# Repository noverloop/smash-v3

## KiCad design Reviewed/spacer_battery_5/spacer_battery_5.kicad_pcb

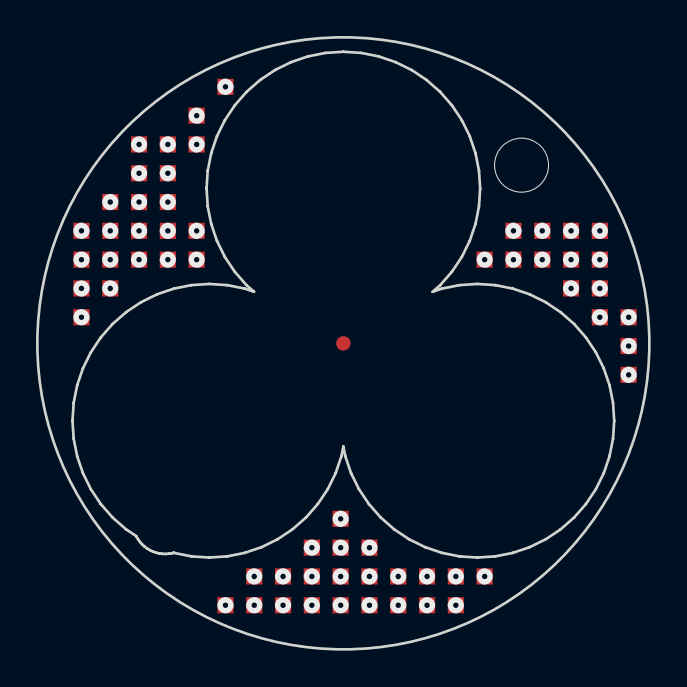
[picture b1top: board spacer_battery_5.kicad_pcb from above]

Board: 2 copper layers, 34.0 x 34.0 mm, 3 parts (1 on the bottom side), 46 nets, no tracks yet.

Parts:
J_spacer_battery_5_top: LGA_lands; J_spacer_battery_5_top
P_spacer_battery_5_bot: LGA_lands; P_spacer_battery_5_bot
SP_battery_5: SP_battery_5; Spacer_Mechanical_34mm

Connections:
3V3: J_spacer_battery_5_top.23, J_spacer_battery_5_top.47, J_spacer_battery_5_top.52, P_spacer_battery_5_bot.23, P_spacer_battery_5_bot.47, P_spacer_battery_5_bot.52
3V3_AON: J_spacer_battery_5_top.24, J_spacer_battery_5_top.48, P_spacer_battery_5_bot.24, P_spacer_battery_5_bot.48
ACTIVATE_CONFIRM: J_spacer_battery_5_top.3, P_spacer_battery_5_bot.3
ACTIVATE_SET: J_spacer_battery_5_top.4, P_spacer_battery_5_bot.4
BAT_PROT: J_spacer_battery_5_top.5, J_spacer_battery_5_top.49, P_spacer_battery_5_bot.5, P_spacer_battery_5_bot.49
BAT_RAW: J_spacer_battery_5_top.6, J_spacer_battery_5_top.50, P_spacer_battery_5_bot.6, P_spacer_battery_5_bot.50
BOOT0: J_spacer_battery_5_top.7, P_spacer_battery_5_bot.7
COMP_5V: J_spacer_battery_5_top.8, J_spacer_battery_5_top.51, P_spacer_battery_5_bot.8, P_spacer_battery_5_bot.51
COMP_SWDCLK: J_spacer_battery_5_top.9, P_spacer_battery_5_bot.9
COMP_SWDIO: J_spacer_battery_5_top.10, P_spacer_battery_5_bot.10
EXT_CAN_RX: J_spacer_battery_5_top.11, P_spacer_battery_5_bot.11
EXT_CAN_TX: J_spacer_battery_5_top.14, P_spacer_battery_5_bot.14
FIN1_AOUT1: J_spacer_battery_5_top.13, P_spacer_battery_5_bot.13
FIN1_AOUT2: J_spacer_battery_5_top.12, P_spacer_battery_5_bot.12
FIN1_BOUT1: J_spacer_battery_5_top.15, P_spacer_battery_5_bot.15
FIN1_BOUT2: J_spacer_battery_5_top.16, P_spacer_battery_5_bot.16
FIN2_AOUT1: J_spacer_battery_5_top.17, P_spacer_battery_5_bot.17
FIN2_AOUT2: J_spacer_battery_5_top.18, P_spacer_battery_5_bot.18
FIN2_BOUT1: J_spacer_battery_5_top.19, P_spacer_battery_5_bot.19
FIN2_BOUT2: J_spacer_battery_5_top.20, P_spacer_battery_5_bot.20
FIN3_AOUT1: J_spacer_battery_5_top.21, P_spacer_battery_5_bot.21
FIN3_AOUT2: J_spacer_battery_5_top.22, P_spacer_battery_5_bot.22
FIN3_BOUT1: J_spacer_battery_5_top.1, P_spacer_battery_5_bot.1
FIN3_BOUT2: J_spacer_battery_5_top.2, P_spacer_battery_5_bot.2
FIN4_AOUT1: J_spacer_battery_5_top.25, P_spacer_battery_5_bot.25
FIN4_AOUT2: J_spacer_battery_5_top.26, P_spacer_battery_5_bot.26
FIN4_BOUT1: J_spacer_battery_5_top.27, P_spacer_battery_5_bot.27
FIN4_BOUT2: J_spacer_battery_5_top.28, P_spacer_battery_5_bot.28
FIN_HALL: J_spacer_battery_5_top.29, P_spacer_battery_5_bot.29
FLEX_GND: J_spacer_battery_5_top.30, J_spacer_battery_5_top.53, J_spacer_battery_5_top.54, J_spacer_battery_5_top.55, J_spacer_battery_5_top.56, J_spacer_battery_5_top.57, J_spacer_battery_5_top.58, J_spacer_battery_5_top.59, J_spacer_battery_5_top.60, P_spacer_battery_5_bot.30, P_spacer_battery_5_bot.53, P_spacer_battery_5_bot.54, P_spacer_battery_5_bot.55, P_spacer_battery_5_bot.56, P_spacer_battery_5_bot.57, P_spacer_battery_5_bot.58, P_spacer_battery_5_bot.59, P_spacer_battery_5_bot.60, SP_battery_5.1
GPIO_EXT_0: J_spacer_battery_5_top.31, P_spacer_battery_5_bot.31
GPIO_EXT_1: J_spacer_battery_5_top.32, P_spacer_battery_5_bot.32
GPIO_EXT_2: J_spacer_battery_5_top.33, P_spacer_battery_5_bot.33
GPIO_EXT_3: J_spacer_battery_5_top.34, P_spacer_battery_5_bot.34
H3LIS_INT1: J_spacer_battery_5_top.35, P_spacer_battery_5_bot.35
I2C3_SCL: J_spacer_battery_5_top.36, P_spacer_battery_5_bot.36
I2C3_SDA: J_spacer_battery_5_top.37, P_spacer_battery_5_bot.37
JUMP_WAKE: J_spacer_battery_5_top.38, P_spacer_battery_5_bot.38
NRST: J_spacer_battery_5_top.39, P_spacer_battery_5_bot.39
SWO: J_spacer_battery_5_top.40, P_spacer_battery_5_bot.40
SYS_I2C_SCL: J_spacer_battery_5_top.41, P_spacer_battery_5_bot.41
SYS_I2C_SDA: J_spacer_battery_5_top.42, P_spacer_battery_5_bot.42
SYS_SPI_CS_FIN: J_spacer_battery_5_top.43, P_spacer_battery_5_bot.43
SYS_SPI_MISO: J_spacer_battery_5_top.44, P_spacer_battery_5_bot.44
SYS_SPI_MOSI: J_spacer_battery_5_top.45, P_spacer_battery_5_bot.45
SYS_SPI_SCLK: J_spacer_battery_5_top.46, P_spacer_battery_5_bot.46

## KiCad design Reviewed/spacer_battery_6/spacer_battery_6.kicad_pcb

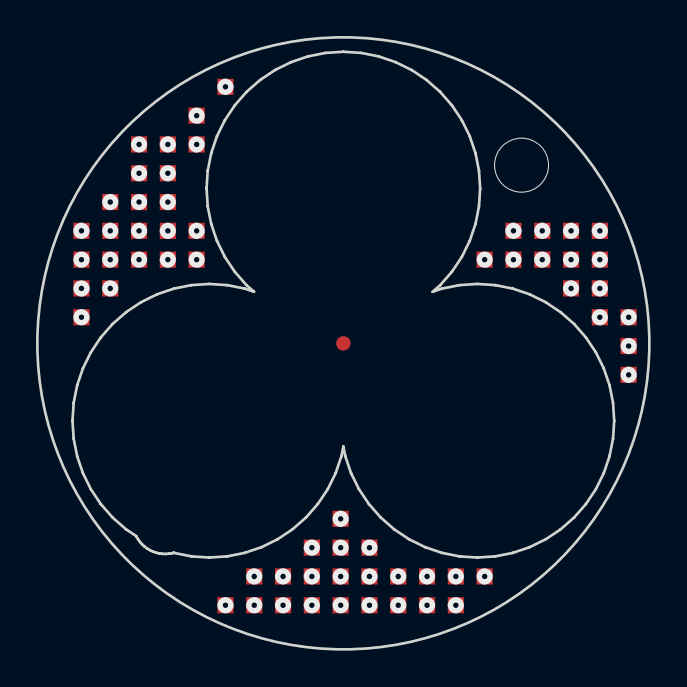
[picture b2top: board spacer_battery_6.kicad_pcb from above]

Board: 2 copper layers, 34.0 x 34.0 mm, 3 parts (1 on the bottom side), 46 nets, no tracks yet.

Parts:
J_spacer_battery_6_top: LGA_lands; J_spacer_battery_6_top
P_spacer_battery_6_bot: LGA_lands; P_spacer_battery_6_bot
SP_battery_6: SP_battery_6; Spacer_Mechanical_34mm

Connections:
3V3: J_spacer_battery_6_top.23, J_spacer_battery_6_top.47, J_spacer_battery_6_top.52, P_spacer_battery_6_bot.23, P_spacer_battery_6_bot.47, P_spacer_battery_6_bot.52
3V3_AON: J_spacer_battery_6_top.24, J_spacer_battery_6_top.48, P_spacer_battery_6_bot.24, P_spacer_battery_6_bot.48
ACTIVATE_CONFIRM: J_spacer_battery_6_top.3, P_spacer_battery_6_bot.3
ACTIVATE_SET: J_spacer_battery_6_top.4, P_spacer_battery_6_bot.4
BAT_PROT: J_spacer_battery_6_top.5, J_spacer_battery_6_top.49, P_spacer_battery_6_bot.5, P_spacer_battery_6_bot.49
BAT_RAW: J_spacer_battery_6_top.6, J_spacer_battery_6_top.50, P_spacer_battery_6_bot.6, P_spacer_battery_6_bot.50
BOOT0: J_spacer_battery_6_top.7, P_spacer_battery_6_bot.7
COMP_5V: J_spacer_battery_6_top.8, J_spacer_battery_6_top.51, P_spacer_battery_6_bot.8, P_spacer_battery_6_bot.51
COMP_SWDCLK: J_spacer_battery_6_top.9, P_spacer_battery_6_bot.9
COMP_SWDIO: J_spacer_battery_6_top.10, P_spacer_battery_6_bot.10
EXT_CAN_RX: J_spacer_battery_6_top.11, P_spacer_battery_6_bot.11
EXT_CAN_TX: J_spacer_battery_6_top.14, P_spacer_battery_6_bot.14
FIN1_AOUT1: J_spacer_battery_6_top.13, P_spacer_battery_6_bot.13
FIN1_AOUT2: J_spacer_battery_6_top.12, P_spacer_battery_6_bot.12
FIN1_BOUT1: J_spacer_battery_6_top.15, P_spacer_battery_6_bot.15
FIN1_BOUT2: J_spacer_battery_6_top.16, P_spacer_battery_6_bot.16
FIN2_AOUT1: J_spacer_battery_6_top.17, P_spacer_battery_6_bot.17
FIN2_AOUT2: J_spacer_battery_6_top.18, P_spacer_battery_6_bot.18
FIN2_BOUT1: J_spacer_battery_6_top.19, P_spacer_battery_6_bot.19
FIN2_BOUT2: J_spacer_battery_6_top.20, P_spacer_battery_6_bot.20
FIN3_AOUT1: J_spacer_battery_6_top.21, P_spacer_battery_6_bot.21
FIN3_AOUT2: J_spacer_battery_6_top.22, P_spacer_battery_6_bot.22
FIN3_BOUT1: J_spacer_battery_6_top.1, P_spacer_battery_6_bot.1
FIN3_BOUT2: J_spacer_battery_6_top.2, P_spacer_battery_6_bot.2
FIN4_AOUT1: J_spacer_battery_6_top.25, P_spacer_battery_6_bot.25
FIN4_AOUT2: J_spacer_battery_6_top.26, P_spacer_battery_6_bot.26
FIN4_BOUT1: J_spacer_battery_6_top.27, P_spacer_battery_6_bot.27
FIN4_BOUT2: J_spacer_battery_6_top.28, P_spacer_battery_6_bot.28
FIN_HALL: J_spacer_battery_6_top.29, P_spacer_battery_6_bot.29
FLEX_GND: J_spacer_battery_6_top.30, J_spacer_battery_6_top.53, J_spacer_battery_6_top.54, J_spacer_battery_6_top.55, J_spacer_battery_6_top.56, J_spacer_battery_6_top.57, J_spacer_battery_6_top.58, J_spacer_battery_6_top.59, J_spacer_battery_6_top.60, P_spacer_battery_6_bot.30, P_spacer_battery_6_bot.53, P_spacer_battery_6_bot.54, P_spacer_battery_6_bot.55, P_spacer_battery_6_bot.56, P_spacer_battery_6_bot.57, P_spacer_battery_6_bot.58, P_spacer_battery_6_bot.59, P_spacer_battery_6_bot.60, SP_battery_6.1
GPIO_EXT_0: J_spacer_battery_6_top.31, P_spacer_battery_6_bot.31
GPIO_EXT_1: J_spacer_battery_6_top.32, P_spacer_battery_6_bot.32
GPIO_EXT_2: J_spacer_battery_6_top.33, P_spacer_battery_6_bot.33
GPIO_EXT_3: J_spacer_battery_6_top.34, P_spacer_battery_6_bot.34
H3LIS_INT1: J_spacer_battery_6_top.35, P_spacer_battery_6_bot.35
I2C3_SCL: J_spacer_battery_6_top.36, P_spacer_battery_6_bot.36
I2C3_SDA: J_spacer_battery_6_top.37, P_spacer_battery_6_bot.37
JUMP_WAKE: J_spacer_battery_6_top.38, P_spacer_battery_6_bot.38
NRST: J_spacer_battery_6_top.39, P_spacer_battery_6_bot.39
SWO: J_spacer_battery_6_top.40, P_spacer_battery_6_bot.40
SYS_I2C_SCL: J_spacer_battery_6_top.41, P_spacer_battery_6_bot.41
SYS_I2C_SDA: J_spacer_battery_6_top.42, P_spacer_battery_6_bot.42
SYS_SPI_CS_FIN: J_spacer_battery_6_top.43, P_spacer_battery_6_bot.43
SYS_SPI_MISO: J_spacer_battery_6_top.44, P_spacer_battery_6_bot.44
SYS_SPI_MOSI: J_spacer_battery_6_top.45, P_spacer_battery_6_bot.45
SYS_SPI_SCLK: J_spacer_battery_6_top.46, P_spacer_battery_6_bot.46

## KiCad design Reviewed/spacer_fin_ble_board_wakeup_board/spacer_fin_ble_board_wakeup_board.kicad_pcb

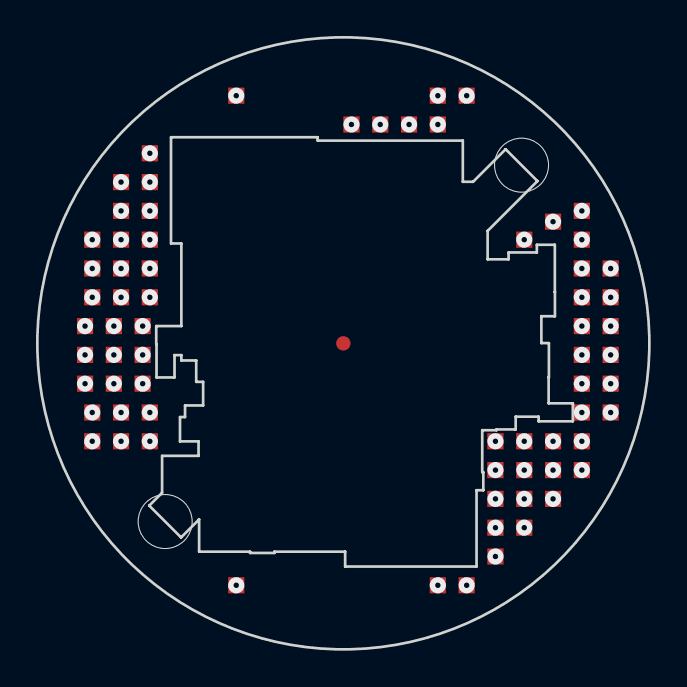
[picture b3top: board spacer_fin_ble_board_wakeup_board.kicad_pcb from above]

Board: 2 copper layers, 34.0 x 34.0 mm, 3 parts (1 on the bottom side), 34 nets, no tracks yet.

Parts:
J_spacer_fin_ble_board_wakeup_board_top: LGA_lands; J_spacer_fin_ble_board_wakeup_board_top
P_spacer_fin_ble_board_wakeup_board_bot: LGA_lands; P_spacer_fin_ble_board_wakeup_board_bot
SP_fin_ble_board_wakeup_board: SP_fin_ble_board_wakeup_board; Spacer_Mechanical_34mm

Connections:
3V3: J_spacer_fin_ble_board_wakeup_board_top.1, J_spacer_fin_ble_board_wakeup_board_top.35, J_spacer_fin_ble_board_wakeup_board_top.41, P_spacer_fin_ble_board_wakeup_board_bot.1, P_spacer_fin_ble_board_wakeup_board_bot.35, P_spacer_fin_ble_board_wakeup_board_bot.41
3V3_AON: J_spacer_fin_ble_board_wakeup_board_top.2, J_spacer_fin_ble_board_wakeup_board_top.36, P_spacer_fin_ble_board_wakeup_board_bot.2, P_spacer_fin_ble_board_wakeup_board_bot.36
ACTIVATE_CONFIRM: J_spacer_fin_ble_board_wakeup_board_top.3, P_spacer_fin_ble_board_wakeup_board_bot.3
ACTIVATE_SET: J_spacer_fin_ble_board_wakeup_board_top.4, P_spacer_fin_ble_board_wakeup_board_bot.4
BAT_CELL1_POS: J_spacer_fin_ble_board_wakeup_board_top.5, P_spacer_fin_ble_board_wakeup_board_bot.5
BAT_CELL2_POS: J_spacer_fin_ble_board_wakeup_board_top.6, P_spacer_fin_ble_board_wakeup_board_bot.6
BAT_CELL3_POS: J_spacer_fin_ble_board_wakeup_board_top.7, P_spacer_fin_ble_board_wakeup_board_bot.7
BAT_PROT: J_spacer_fin_ble_board_wakeup_board_top.8, J_spacer_fin_ble_board_wakeup_board_top.37, P_spacer_fin_ble_board_wakeup_board_bot.8, P_spacer_fin_ble_board_wakeup_board_bot.37
BAT_RAW: J_spacer_fin_ble_board_wakeup_board_top.9, J_spacer_fin_ble_board_wakeup_board_top.38, P_spacer_fin_ble_board_wakeup_board_bot.9, P_spacer_fin_ble_board_wakeup_board_bot.38
BOOT0: J_spacer_fin_ble_board_wakeup_board_top.10, P_spacer_fin_ble_board_wakeup_board_bot.10
COMP_5V: J_spacer_fin_ble_board_wakeup_board_top.11, J_spacer_fin_ble_board_wakeup_board_top.39, P_spacer_fin_ble_board_wakeup_board_bot.11, P_spacer_fin_ble_board_wakeup_board_bot.39
COMP_5V_RAW: J_spacer_fin_ble_board_wakeup_board_top.12, J_spacer_fin_ble_board_wakeup_board_top.40, P_spacer_fin_ble_board_wakeup_board_bot.12, P_spacer_fin_ble_board_wakeup_board_bot.40
COMP_OUT: J_spacer_fin_ble_board_wakeup_board_top.13, P_spacer_fin_ble_board_wakeup_board_bot.13
COMP_SWDCLK: J_spacer_fin_ble_board_wakeup_board_top.14, P_spacer_fin_ble_board_wakeup_board_bot.14
COMP_SWDIO: J_spacer_fin_ble_board_wakeup_board_top.15, P_spacer_fin_ble_board_wakeup_board_bot.15
EXT_CAN_RX: J_spacer_fin_ble_board_wakeup_board_top.16, P_spacer_fin_ble_board_wakeup_board_bot.16
EXT_CAN_TX: J_spacer_fin_ble_board_wakeup_board_top.17, P_spacer_fin_ble_board_wakeup_board_bot.17
FLEX_GND: J_spacer_fin_ble_board_wakeup_board_top.18, J_spacer_fin_ble_board_wakeup_board_top.42, J_spacer_fin_ble_board_wakeup_board_top.43, J_spacer_fin_ble_board_wakeup_board_top.44, J_spacer_fin_ble_board_wakeup_board_top.45, J_spacer_fin_ble_board_wakeup_board_top.46, J_spacer_fin_ble_board_wakeup_board_top.47, J_spacer_fin_ble_board_wakeup_board_top.48, J_spacer_fin_ble_board_wakeup_board_top.49, J_spacer_fin_ble_board_wakeup_board_top.50, J_spacer_fin_ble_board_wakeup_board_top.51, J_spacer_fin_ble_board_wakeup_board_top.52, J_spacer_fin_ble_board_wakeup_board_top.53, J_spacer_fin_ble_board_wakeup_board_top.54, J_spacer_fin_ble_board_wakeup_board_top.55, J_spacer_fin_ble_board_wakeup_board_top.56, J_spacer_fin_ble_board_wakeup_board_top.57, J_spacer_fin_ble_board_wakeup_board_top.58, J_spacer_fin_ble_board_wakeup_board_top.59, J_spacer_fin_ble_board_wakeup_board_top.60, J_spacer_fin_ble_board_wakeup_board_top.61, J_spacer_fin_ble_board_wakeup_board_top.62, J_spacer_fin_ble_board_wakeup_board_top.63, J_spacer_fin_ble_board_wakeup_board_top.64, J_spacer_fin_ble_board_wakeup_board_top.65, J_spacer_fin_ble_board_wakeup_board_top.66, J_spacer_fin_ble_board_wakeup_board_top.67, J_spacer_fin_ble_board_wakeup_board_top.68, J_spacer_fin_ble_board_wakeup_board_top.69, P_spacer_fin_ble_board_wakeup_board_bot.18, P_spacer_fin_ble_board_wakeup_board_bot.42, P_spacer_fin_ble_board_wakeup_board_bot.43, P_spacer_fin_ble_board_wakeup_board_bot.44, P_spacer_fin_ble_board_wakeup_board_bot.45, P_spacer_fin_ble_board_wakeup_board_bot.46, P_spacer_fin_ble_board_wakeup_board_bot.47, P_spacer_fin_ble_board_wakeup_board_bot.48, P_spacer_fin_ble_board_wakeup_board_bot.49, P_spacer_fin_ble_board_wakeup_board_bot.50, P_spacer_fin_ble_board_wakeup_board_bot.51, P_spacer_fin_ble_board_wakeup_board_bot.52, P_spacer_fin_ble_board_wakeup_board_bot.53, P_spacer_fin_ble_board_wakeup_board_bot.54, P_spacer_fin_ble_board_wakeup_board_bot.55, P_spacer_fin_ble_board_wakeup_board_bot.56, P_spacer_fin_ble_board_wakeup_board_bot.57, P_spacer_fin_ble_board_wakeup_board_bot.58, P_spacer_fin_ble_board_wakeup_board_bot.59, P_spacer_fin_ble_board_wakeup_board_bot.60, P_spacer_fin_ble_board_wakeup_board_bot.61, P_spacer_fin_ble_board_wakeup_board_bot.62, P_spacer_fin_ble_board_wakeup_board_bot.63, P_spacer_fin_ble_board_wakeup_board_bot.64, P_spacer_fin_ble_board_wakeup_board_bot.65, P_spacer_fin_ble_board_wakeup_board_bot.66, P_spacer_fin_ble_board_wakeup_board_bot.67, P_spacer_fin_ble_board_wakeup_board_bot.68, P_spacer_fin_ble_board_wakeup_board_bot.69, SP_fin_ble_board_wakeup_board.1
GPIO_EXT_0: J_spacer_fin_ble_board_wakeup_board_top.19, P_spacer_fin_ble_board_wakeup_board_bot.19
GPIO_EXT_1: J_spacer_fin_ble_board_wakeup_board_top.20, P_spacer_fin_ble_board_wakeup_board_bot.20
GPIO_EXT_2: J_spacer_fin_ble_board_wakeup_board_top.21, P_spacer_fin_ble_board_wakeup_board_bot.21
GPIO_EXT_3: J_spacer_fin_ble_board_wakeup_board_top.22, P_spacer_fin_ble_board_wakeup_board_bot.22
H3LIS_INT1: J_spacer_fin_ble_board_wakeup_board_top.23, P_spacer_fin_ble_board_wakeup_board_bot.23
I2C3_SCL: J_spacer_fin_ble_board_wakeup_board_top.24, P_spacer_fin_ble_board_wakeup_board_bot.24
I2C3_SDA: J_spacer_fin_ble_board_wakeup_board_top.25, P_spacer_fin_ble_board_wakeup_board_bot.25
JUMP_WAKE: J_spacer_fin_ble_board_wakeup_board_top.26, P_spacer_fin_ble_board_wakeup_board_bot.26
NRST: J_spacer_fin_ble_board_wakeup_board_top.27, P_spacer_fin_ble_board_wakeup_board_bot.27
SWO: J_spacer_fin_ble_board_wakeup_board_top.28, P_spacer_fin_ble_board_wakeup_board_bot.28
SYS_I2C_SCL: J_spacer_fin_ble_board_wakeup_board_top.29, P_spacer_fin_ble_board_wakeup_board_bot.29
SYS_I2C_SDA: J_spacer_fin_ble_board_wakeup_board_top.30, P_spacer_fin_ble_board_wakeup_board_bot.30
SYS_SPI_CS_FIN: J_spacer_fin_ble_board_wakeup_board_top.31, P_spacer_fin_ble_board_wakeup_board_bot.31
SYS_SPI_MISO: J_spacer_fin_ble_board_wakeup_board_top.32, P_spacer_fin_ble_board_wakeup_board_bot.32
SYS_SPI_MOSI: J_spacer_fin_ble_board_wakeup_board_top.33, P_spacer_fin_ble_board_wakeup_board_bot.33
SYS_SPI_SCLK: J_spacer_fin_ble_board_wakeup_board_top.34, P_spacer_fin_ble_board_wakeup_board_bot.34

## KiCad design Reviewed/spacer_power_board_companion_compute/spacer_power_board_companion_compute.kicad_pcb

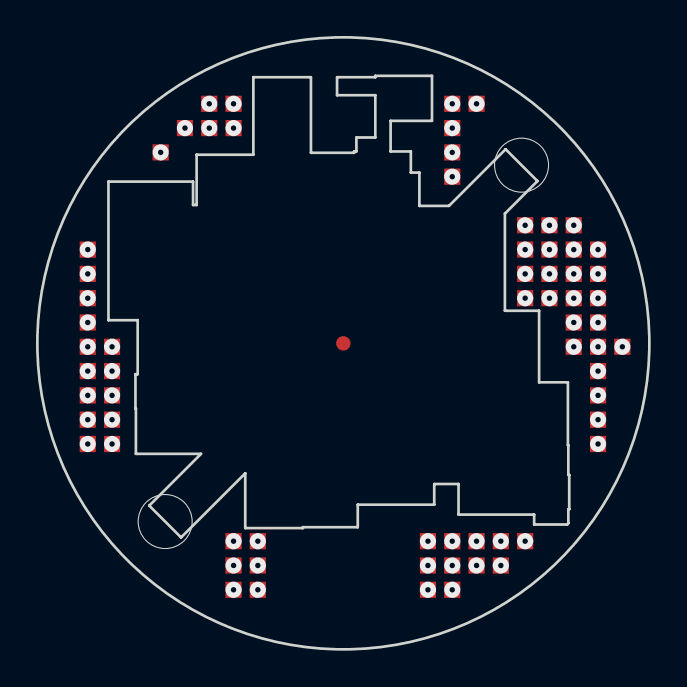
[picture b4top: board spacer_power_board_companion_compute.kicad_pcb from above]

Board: 2 copper layers, 34.0 x 34.0 mm, 3 parts (1 on the bottom side), 56 nets, no tracks yet.

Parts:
J_spacer_power_board_companion_compute_top: LGA_lands; J_spacer_power_board_companion_compute_top
P_spacer_power_board_companion_compute_bot: LGA_lands; P_spacer_power_board_companion_compute_bot
SP_power_board_companion_compute: SP_power_board_companion_compute; Spacer_Mechanical_34mm

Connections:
3V3: J_spacer_power_board_companion_compute_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.1, J_spacer_power_board_companion_compute_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.57, P_spacer_power_board_companion_compute_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.1, P_spacer_power_board_companion_compute_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.57
ACTIVATE_CONFIRM: J_spacer_power_board_companion_compute_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.2, P_spacer_power_board_companion_compute_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.2
ACTIVATE_SET: J_spacer_power_board_companion_compute_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.3, P_spacer_power_board_companion_compute_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.3
BAT_ISO_DRIVE: J_spacer_power_board_companion_compute_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.4, P_spacer_power_board_companion_compute_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.4
BAT_PROT: J_spacer_power_board_companion_compute_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.5, J_spacer_power_board_companion_compute_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.58, P_spacer_power_board_companion_compute_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.5, P_spacer_power_board_companion_compute_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.58
BOOT0: J_spacer_power_board_companion_compute_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.6, P_spacer_power_board_companion_compute_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.6
COMP_0V9: J_spacer_power_board_companion_compute_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.8, J_spacer_power_board_companion_compute_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.60, P_spacer_power_board_companion_compute_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.8, P_spacer_power_board_companion_compute_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.60
COMP_0V82: J_spacer_power_board_companion_compute_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.7, J_spacer_power_board_companion_compute_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.59, P_spacer_power_board_companion_compute_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.7, P_spacer_power_board_companion_compute_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.59
COMP_1V2: J_spacer_power_board_companion_compute_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.9, J_spacer_power_board_companion_compute_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.61, P_spacer_power_board_companion_compute_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.9, P_spacer_power_board_companion_compute_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.61
COMP_1V8: J_spacer_power_board_companion_compute_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.10, J_spacer_power_board_companion_compute_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.62, P_spacer_power_board_companion_compute_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.10, P_spacer_power_board_companion_compute_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.62
COMP_2V8: J_spacer_power_board_companion_compute_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.11, J_spacer_power_board_companion_compute_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.63, P_spacer_power_board_companion_compute_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.11, P_spacer_power_board_companion_compute_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.63
COMP_3V3: J_spacer_power_board_companion_compute_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.12, J_spacer_power_board_companion_compute_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.64, P_spacer_power_board_companion_compute_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.12, P_spacer_power_board_companion_compute_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.64
COMP_5V: J_spacer_power_board_companion_compute_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.13, J_spacer_power_board_companion_compute_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.65, P_spacer_power_board_companion_compute_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.13, P_spacer_power_board_companion_compute_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.65
COMP_OUT: J_spacer_power_board_companion_compute_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.14, P_spacer_power_board_companion_compute_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.14
COMP_SWDCLK: J_spacer_power_board_companion_compute_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.15, P_spacer_power_board_companion_compute_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.15
COMP_SWDIO: J_spacer_power_board_companion_compute_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.16, P_spacer_power_board_companion_compute_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.16
COMP_VPP: J_spacer_power_board_companion_compute_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.17, J_spacer_power_board_companion_compute_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.66, P_spacer_power_board_companion_compute_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.17, P_spacer_power_board_companion_compute_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.66
EXT_CAN_RX: J_spacer_power_board_companion_compute_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.18, P_spacer_power_board_companion_compute_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.18
EXT_CAN_TX: J_spacer_power_board_companion_compute_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.19, P_spacer_power_board_companion_compute_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.19
FLEX_GND: J_spacer_power_board_companion_compute_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.20, P_spacer_power_board_companion_compute_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.20, SP_power_board_companion_compute.1
GPIO_EXT_0: J_spacer_power_board_companion_compute_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.21, P_spacer_power_board_companion_compute_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.21
GPIO_EXT_1: J_spacer_power_board_companion_compute_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.22, P_spacer_power_board_companion_compute_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.22
GPIO_EXT_2: J_spacer_power_board_companion_compute_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.23, P_spacer_power_board_companion_compute_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.23
GPIO_EXT_3: J_spacer_power_board_companion_compute_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.24, P_spacer_power_board_companion_compute_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.24
H3LIS_INT1: J_spacer_power_board_companion_compute_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.25, P_spacer_power_board_companion_compute_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.25
I2C2_SCL: J_spacer_power_board_companion_compute_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.26, P_spacer_power_board_companion_compute_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.26
I2C2_SDA: J_spacer_power_board_companion_compute_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.27, P_spacer_power_board_companion_compute_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.27
I2C3_SCL: J_spacer_power_board_companion_compute_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.28, P_spacer_power_board_companion_compute_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.28
I2C3_SDA: J_spacer_power_board_companion_compute_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.29, P_spacer_power_board_companion_compute_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.29
IMU1_INT: J_spacer_power_board_companion_compute_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.30, P_spacer_power_board_companion_compute_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.30
IMU2_INT: J_spacer_power_board_companion_compute_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.31, P_spacer_power_board_companion_compute_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.31
IMU3_INT: J_spacer_power_board_companion_compute_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.32, P_spacer_power_board_companion_compute_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.32
IR_TX: J_spacer_power_board_companion_compute_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.33, P_spacer_power_board_companion_compute_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.33
IR_WAKE: J_spacer_power_board_companion_compute_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.34, P_spacer_power_board_companion_compute_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.34
MAG_DRDY: J_spacer_power_board_companion_compute_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.35, P_spacer_power_board_companion_compute_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.35
NRST: J_spacer_power_board_companion_compute_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.36, P_spacer_power_board_companion_compute_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.36
PMIC_PWR_OK: J_spacer_power_board_companion_compute_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.37, P_spacer_power_board_companion_compute_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.37
PWR_HOLD: J_spacer_power_board_companion_compute_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.38, P_spacer_power_board_companion_compute_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.38
SWO: J_spacer_power_board_companion_compute_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.39, P_spacer_power_board_companion_compute_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.39
SYS_I2C_SCL: J_spacer_power_board_companion_compute_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.40, P_spacer_power_board_companion_compute_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.40
SYS_I2C_SDA: J_spacer_power_board_companion_compute_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.41, P_spacer_power_board_companion_compute_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.41
SYS_SPI_CS_FIN: J_spacer_power_board_companion_compute_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.42, P_spacer_power_board_companion_compute_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.42
SYS_SPI_MISO: J_spacer_power_board_companion_compute_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.43, P_spacer_power_board_companion_compute_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.43
SYS_SPI_MOSI: J_spacer_power_board_companion_compute_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.44, P_spacer_power_board_companion_compute_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.44
SYS_SPI_SCLK: J_spacer_power_board_companion_compute_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.45, P_spacer_power_board_companion_compute_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.45
TMP1_ALERT: J_spacer_power_board_companion_compute_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.46, P_spacer_power_board_companion_compute_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.46
USB_VBUS: J_spacer_power_board_companion_compute_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.47, P_spacer_power_board_companion_compute_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.47
WBA_BOOT0: J_spacer_power_board_companion_compute_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.48, P_spacer_power_board_companion_compute_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.48
WBA_HCI_IRQ: J_spacer_power_board_companion_compute_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.49, P_spacer_power_board_companion_compute_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.49
WBA_HCI_MISO: J_spacer_power_board_companion_compute_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.50, P_spacer_power_board_companion_compute_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.50
WBA_HCI_MOSI: J_spacer_power_board_companion_compute_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.51, P_spacer_power_board_companion_compute_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.51
WBA_HCI_NSS: J_spacer_power_board_companion_compute_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.52, P_spacer_power_board_companion_compute_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.52
WBA_HCI_SCK: J_spacer_power_board_companion_compute_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.53, P_spacer_power_board_companion_compute_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.53
WBA_RST_CMD: J_spacer_power_board_companion_compute_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.54, P_spacer_power_board_companion_compute_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.54
WBA_UART_RX: J_spacer_power_board_companion_compute_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.55, P_spacer_power_board_companion_compute_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.55
WBA_UART_TX: J_spacer_power_board_companion_compute_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.56, P_spacer_power_board_companion_compute_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.56

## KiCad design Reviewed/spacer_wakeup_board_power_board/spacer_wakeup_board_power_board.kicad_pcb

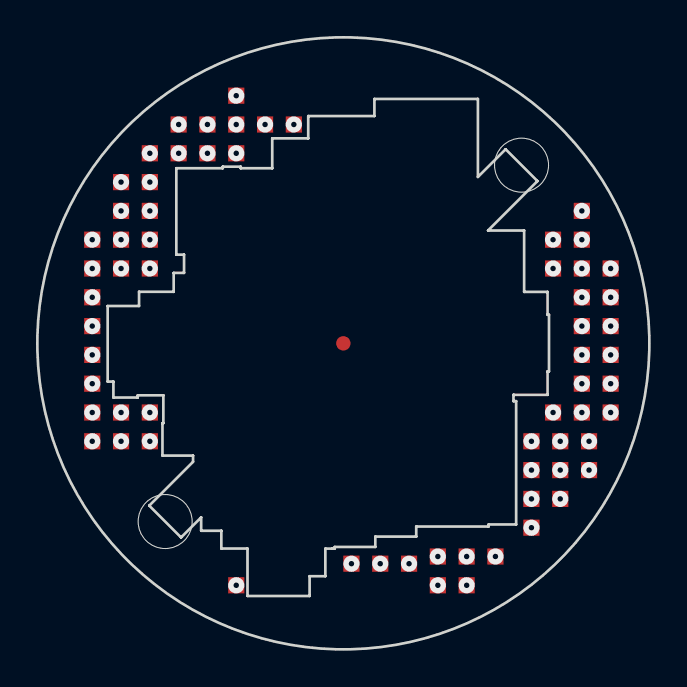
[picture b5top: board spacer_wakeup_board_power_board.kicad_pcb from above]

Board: 2 copper layers, 34.0 x 34.0 mm, 3 parts (1 on the bottom side), 54 nets, no tracks yet.

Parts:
J_spacer_wakeup_board_power_board_top: LGA_lands; J_spacer_wakeup_board_power_board_top
P_spacer_wakeup_board_power_board_bot: LGA_lands; P_spacer_wakeup_board_power_board_bot
SP_wakeup_board_power_board: SP_wakeup_board_power_board; Spacer_Mechanical_34mm

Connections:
3V3: J_spacer_wakeup_board_power_board_top.1, J_spacer_wakeup_board_power_board_top.55, J_spacer_wakeup_board_power_board_top.62, P_spacer_wakeup_board_power_board_bot.1, P_spacer_wakeup_board_power_board_bot.55, P_spacer_wakeup_board_power_board_bot.62
ACTIVATE_CONFIRM: J_spacer_wakeup_board_power_board_top.2, P_spacer_wakeup_board_power_board_bot.2
ACTIVATE_SET: J_spacer_wakeup_board_power_board_top.3, P_spacer_wakeup_board_power_board_bot.3
BAT_CELL1_POS: J_spacer_wakeup_board_power_board_top.4, P_spacer_wakeup_board_power_board_bot.4
BAT_CELL2_POS: J_spacer_wakeup_board_power_board_top.5, P_spacer_wakeup_board_power_board_bot.5
BAT_CELL3_POS: J_spacer_wakeup_board_power_board_top.6, P_spacer_wakeup_board_power_board_bot.6
BAT_PROT: J_spacer_wakeup_board_power_board_top.7, J_spacer_wakeup_board_power_board_top.56, P_spacer_wakeup_board_power_board_bot.7, P_spacer_wakeup_board_power_board_bot.56
BAT_RAW: J_spacer_wakeup_board_power_board_top.8, J_spacer_wakeup_board_power_board_top.57, P_spacer_wakeup_board_power_board_bot.8, P_spacer_wakeup_board_power_board_bot.57
BOOT0: J_spacer_wakeup_board_power_board_top.9, P_spacer_wakeup_board_power_board_bot.9
COMP_1V8: J_spacer_wakeup_board_power_board_top.10, J_spacer_wakeup_board_power_board_top.58, P_spacer_wakeup_board_power_board_bot.10, P_spacer_wakeup_board_power_board_bot.58
COMP_5V: J_spacer_wakeup_board_power_board_top.11, J_spacer_wakeup_board_power_board_top.59, P_spacer_wakeup_board_power_board_bot.11, P_spacer_wakeup_board_power_board_bot.59
COMP_5V_RAW: J_spacer_wakeup_board_power_board_top.12, J_spacer_wakeup_board_power_board_top.60, P_spacer_wakeup_board_power_board_bot.12, P_spacer_wakeup_board_power_board_bot.60
COMP_OUT: J_spacer_wakeup_board_power_board_top.13, P_spacer_wakeup_board_power_board_bot.13
COMP_SWDCLK: J_spacer_wakeup_board_power_board_top.14, P_spacer_wakeup_board_power_board_bot.14
COMP_SWDIO: J_spacer_wakeup_board_power_board_top.15, P_spacer_wakeup_board_power_board_bot.15
EXT_CAN_RX: J_spacer_wakeup_board_power_board_top.16, P_spacer_wakeup_board_power_board_bot.16
EXT_CAN_TX: J_spacer_wakeup_board_power_board_top.17, P_spacer_wakeup_board_power_board_bot.17
FLEX_GND: J_spacer_wakeup_board_power_board_top.18, J_spacer_wakeup_board_power_board_top.63, J_spacer_wakeup_board_power_board_top.64, J_spacer_wakeup_board_power_board_top.65, P_spacer_wakeup_board_power_board_bot.18, P_spacer_wakeup_board_power_board_bot.63, P_spacer_wakeup_board_power_board_bot.64, P_spacer_wakeup_board_power_board_bot.65, SP_wakeup_board_power_board.1
GPIO_EXT_0: J_spacer_wakeup_board_power_board_top.19, P_spacer_wakeup_board_power_board_bot.19
GPIO_EXT_1: J_spacer_wakeup_board_power_board_top.20, P_spacer_wakeup_board_power_board_bot.20
GPIO_EXT_2: J_spacer_wakeup_board_power_board_top.21, P_spacer_wakeup_board_power_board_bot.21
GPIO_EXT_3: J_spacer_wakeup_board_power_board_top.22, P_spacer_wakeup_board_power_board_bot.22
H3LIS_INT1: J_spacer_wakeup_board_power_board_top.23, P_spacer_wakeup_board_power_board_bot.23
I2C2_SCL: J_spacer_wakeup_board_power_board_top.24, P_spacer_wakeup_board_power_board_bot.24
I2C2_SDA: J_spacer_wakeup_board_power_board_top.25, P_spacer_wakeup_board_power_board_bot.25
I2C3_SCL: J_spacer_wakeup_board_power_board_top.26, P_spacer_wakeup_board_power_board_bot.26
I2C3_SDA: J_spacer_wakeup_board_power_board_top.27, P_spacer_wakeup_board_power_board_bot.27
IMU1_INT: J_spacer_wakeup_board_power_board_top.28, P_spacer_wakeup_board_power_board_bot.28
IMU2_INT: J_spacer_wakeup_board_power_board_top.29, P_spacer_wakeup_board_power_board_bot.29
IMU3_INT: J_spacer_wakeup_board_power_board_top.30, P_spacer_wakeup_board_power_board_bot.30
IR_TX: J_spacer_wakeup_board_power_board_top.31, P_spacer_wakeup_board_power_board_bot.31
IR_WAKE: J_spacer_wakeup_board_power_board_top.32, P_spacer_wakeup_board_power_board_bot.32
MAG_DRDY: J_spacer_wakeup_board_power_board_top.33, P_spacer_wakeup_board_power_board_bot.33
MAIN_SW_GATE: J_spacer_wakeup_board_power_board_top.34, P_spacer_wakeup_board_power_board_bot.34
NRST: J_spacer_wakeup_board_power_board_top.35, P_spacer_wakeup_board_power_board_bot.35
PWR_HOLD: J_spacer_wakeup_board_power_board_top.36, P_spacer_wakeup_board_power_board_bot.36
REG_IN_MAIN: J_spacer_wakeup_board_power_board_top.37, J_spacer_wakeup_board_power_board_top.61, P_spacer_wakeup_board_power_board_bot.37, P_spacer_wakeup_board_power_board_bot.61
SWO: J_spacer_wakeup_board_power_board_top.38, P_spacer_wakeup_board_power_board_bot.38
SYS_I2C_SCL: J_spacer_wakeup_board_power_board_top.39, P_spacer_wakeup_board_power_board_bot.39
SYS_I2C_SDA: J_spacer_wakeup_board_power_board_top.40, P_spacer_wakeup_board_power_board_bot.40
SYS_SPI_CS_FIN: J_spacer_wakeup_board_power_board_top.41, P_spacer_wakeup_board_power_board_bot.41
SYS_SPI_MISO: J_spacer_wakeup_board_power_board_top.42, P_spacer_wakeup_board_power_board_bot.42
SYS_SPI_MOSI: J_spacer_wakeup_board_power_board_top.43, P_spacer_wakeup_board_power_board_bot.43
SYS_SPI_SCLK: J_spacer_wakeup_board_power_board_top.44, P_spacer_wakeup_board_power_board_bot.44
USBWK_GATE: J_spacer_wakeup_board_power_board_top.45, P_spacer_wakeup_board_power_board_bot.45
WBA_BOOT0: J_spacer_wakeup_board_power_board_top.46, P_spacer_wakeup_board_power_board_bot.46
WBA_HCI_IRQ: J_spacer_wakeup_board_power_board_top.47, P_spacer_wakeup_board_power_board_bot.47
WBA_HCI_MISO: J_spacer_wakeup_board_power_board_top.48, P_spacer_wakeup_board_power_board_bot.48
WBA_HCI_MOSI: J_spacer_wakeup_board_power_board_top.49, P_spacer_wakeup_board_power_board_bot.49
WBA_HCI_NSS: J_spacer_wakeup_board_power_board_top.50, P_spacer_wakeup_board_power_board_bot.50
WBA_HCI_SCK: J_spacer_wakeup_board_power_board_top.51, P_spacer_wakeup_board_power_board_bot.51
WBA_RST_CMD: J_spacer_wakeup_board_power_board_top.52, P_spacer_wakeup_board_power_board_bot.52
WBA_UART_RX: J_spacer_wakeup_board_power_board_top.53, P_spacer_wakeup_board_power_board_bot.53
WBA_UART_TX: J_spacer_wakeup_board_power_board_top.54, P_spacer_wakeup_board_power_board_bot.54
